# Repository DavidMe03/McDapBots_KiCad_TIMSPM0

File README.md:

# McDap Bots Pedagogical Robot

This project was created as a capstone project for the University of Virginia Department of Electrical and Computer Engineering. Our goal was to create a small robot which could be programmed by students, for use as a teaching aide in an embedded systems course. This repository contains the hardware files specific to the robot's main board.

**Authors**
- Colby Wise
- Pratik Pandit
- Austen Yun 
- David Merino
- Marc Rosenthal

**Advisors**: Todd DeLong and Adam Barnes 

**Features at a glance**
- 2 motors (PWM controlled), OLED screen (I2C), reflectance sensor (I2C), bump switches (GPIO), Bluetooth (UART), and infrared sensors (ADC)
- battery charging port and battery voltage display (press button to enable)
- support for TI and STM microcontrollers

## What is contained here

**Project Symbols/Footprints**

Symbols that are specific to this project such as the robot chassis. 

**Schematic File**

KiCad schematic file that shows the electrical connections of each component of the robot. 

**Layout File**

KiCad layout file that shows how the components are placed and routed on the PCB. 

**Bill of Materials Files**

BOM.xlsx contains a list of all the parts needed for the PCB.

Digikey_Parts_List.xlsx can be uploaded to Digikey to select the parts needed for one copy of this board.

## How to use this repository
1. Copy the repository locally to your computer
2. Using KiCad 8.0 (or higher version) open the file `MotorBoardv3_2.kicad_pro`
3. Generate necessary gerber files and order components
4. Follow the provided construction guide to build the robot

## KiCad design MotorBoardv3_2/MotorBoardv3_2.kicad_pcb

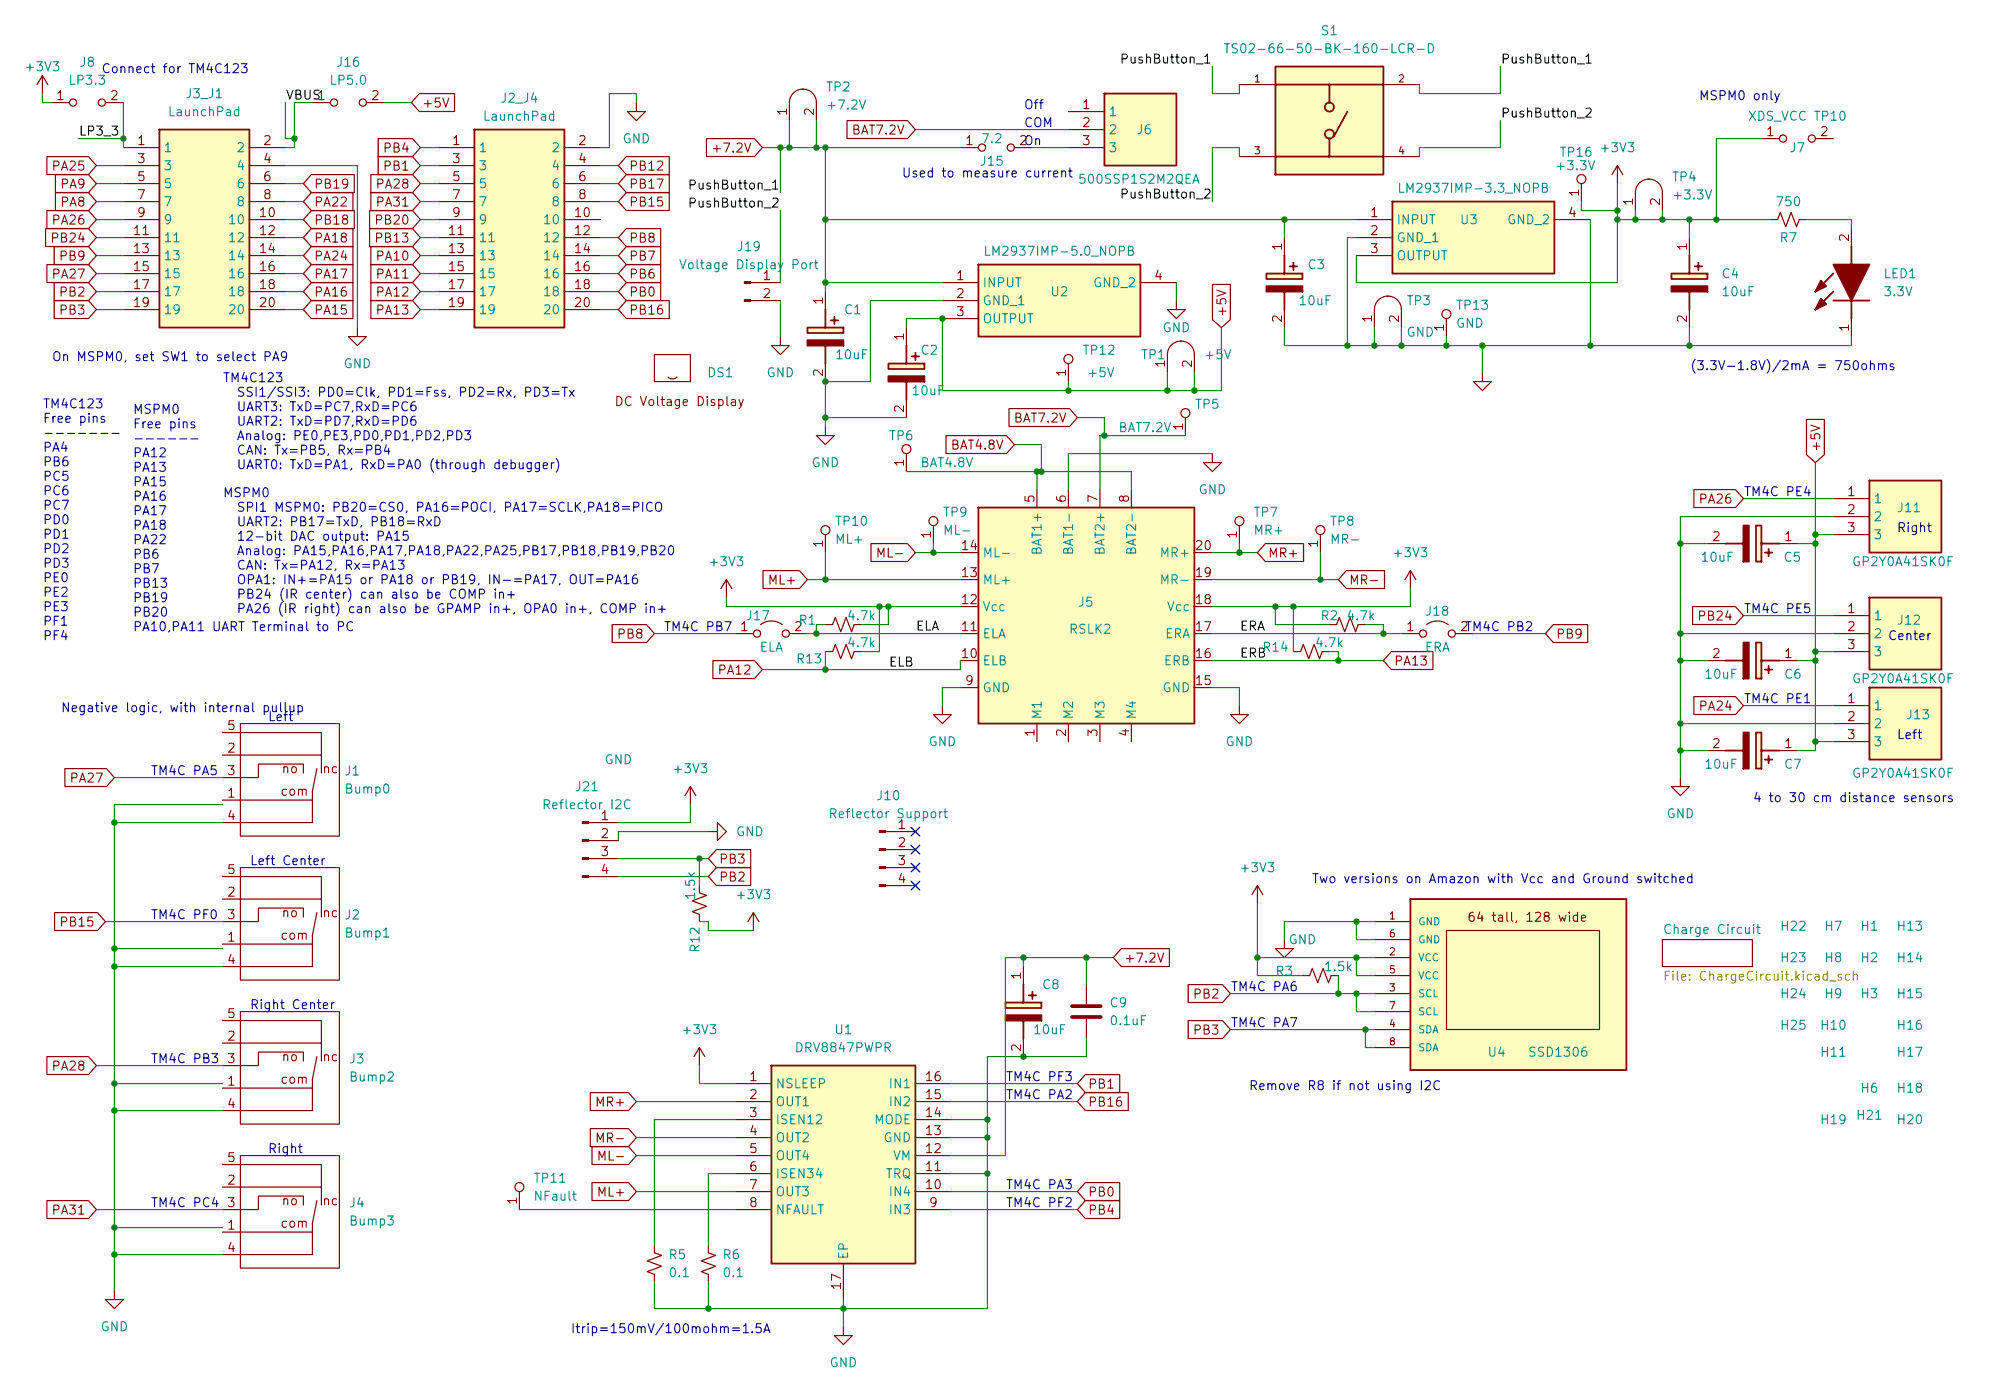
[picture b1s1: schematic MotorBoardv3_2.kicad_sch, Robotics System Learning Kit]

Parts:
C1, C2, C3, C4, C5, C6, C7, C8: 10uF; CAPPM3528X210N; Mouser Part Number 581-TAJB106K020R
C9: 0.1uF; C_0603_1608Metric; LCSC C5186689
DS1: PRT-14313
H1, H2, H3, H6, H7, H8, H9, H10, H11, H13, H14, H15, H16, H17, H18, H19, H20, H21, H22, H23, H24, H25: MountingHole_4_40
J1: Bump0; D2F-01L30-D3_5pin
J2: Bump1; D2F-01L30-D3_5pin
J2_J4, J3_J1: LaunchPad; Mouser Part Number 855-M20-8761042P
J3: Bump2; D2F-01L30-D3_5pin
J4: Bump3; D2F-01L30-D3_5pin
J5: RSLK2; RSLK_Chassis
J6: 500SSP1S2M2QEA; Mouser Part Number 612-500SSP1S2M2QEA
J7: XDS_VCC TP10; PinHeader_1x02_P2.54mm_Vertical; LCSC C5172712
J8: LP3.3; PinHeader_1x02_P2.54mm_Vertical; LCSC C5172712
J10: Reflector Support; PinHeader_1x04_P2.54mm_Vertical
J11, J12, J13: GP2Y0A41SK0F; SHDR3W50P0X200_1X3_650X240X440P; Mouser Part Number 855-M22-7130342
J15: 7.2; PinHeader_1x02_P2.54mm_Vertical; LCSC C5172712
J16: LP5.0; PinHeader_1x02_P2.54mm_Vertical; LCSC C5172712
J17: ELA; PinHeader_1x02_P2.54mm_Vertical
J18: ERA; PinHeader_1x02_P2.54mm_Vertical
J19: Voltage Display Port; SolderWire-0.15sqmm_1x02_P4mm_D0.5mm_OD1.5mm_Relief
J21: Reflector I2C; PinHeader_1x04_P2.54mm_Vertical
LED1: 3.3V; APT1608CGCK; Mouser Part Number 604-APTD1608LSECKJ3F
R1, R2, R13, R14: 4.7k; R_0603_1608Metric; LCSC C23162
R3, R12: 1.5k; R_0603_1608Metric; LCSC C216914
R5, R6: 0.1; R_1206_3216Metric; LCSC C2889036
R7: 750; R_0603_1608Metric; LCSC C365210
S1: TS02-66-50-BK-160-LCR-D; SW_TS02-66-50-BK-160-LCR-D; PARTREV 1.0
TP1: +5V; Testpoint_1x02_P2.54mm
TP2: +7.2V; Testpoint_1x02_P2.54mm
TP3: GND; Testpoint_1x02_P2.54mm
TP4: +3.3V; Testpoint_1x02_P2.54mm
TP5: BAT7.2V; Testpoint_1x1
TP6: BAT4.8V; Testpoint_1x1
TP7: MR+; Testpoint_1x1
TP8: MR-; Testpoint_1x1
TP9: ML-; Testpoint_1x1
TP10: ML+; Testpoint_1x1
TP11: NFault; Testpoint_1x1
TP12: +5V; Testpoint_1x1
TP13: GND; Testpoint_1x1
TP16: +3.3V; Testpoint_1x1
U1: DRV8847PWPR; SOP65P640X120-17N; Mouser Part Number 595-DRV8847PWPR
U2: LM2937IMP-5.0_NOPB; SOT230P700X180-4N; Mouser Part Number 926-LM2937IMP5.0NOPB
U3: LM2937IMP-3.3_NOPB; SOT230P700X180-4N; Mouser Part Number 926-LM2937IMP3.3NOPB
U4: SSD1306

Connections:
+3V3: C4.1 (+), J5.12 (Vcc), J5.18 (Vcc), J7.1 (A), J8.1 (A), J21.1, R1.2, R2.1, R3.1, R7.2, R12.1, R13.2, R14.1, TP4.1 (A), TP4.2 (B), TP16.1 (A), U1.1 (NSLEEP), U3.3 (OUTPUT), U4.2 (VCC), U4.5 (VCC)
+5V: C2.1 (+), C5.1 (+), C6.1 (+), C7.1 (+), J11.3, J12.3, J13.3, J16.2 (B), TP1.1 (A), TP1.2 (B), TP12.1 (A), U2.3 (OUTPUT)
+7.2V: C1.1 (+), C3.1 (+), C8.1 (+), C9.1, J15.1 (A), S1.1, S1.2, TP2.1 (A), TP2.2 (B), U1.12 (VM), U2.1 (INPUT), U3.1 (INPUT)
/ELA: J5.11 (ELA), J17.2 (B), R1.1
/ERA: J5.17 (ERA), J18.1 (A), R2.2
/LP3_3: J3_J1.1, J8.2 (B)
/PushButton_2: J19.1, S1.3, S1.4
/VBUS: J3_J1.2, J16.1 (A)
BAT4.8V: J5.5 (BAT1+), J5.8 (BAT2-), TP6.1 (A)
BAT7.2V: J5.7 (BAT2+), J6.2, TP5.1 (A); also elsewhere on the board
GND: C1.2 (-), C2.2 (-), C3.2 (-), C4.2 (-), C5.2 (-), C6.2 (-), C7.2 (-), C8.2 (-), C9.2, J1.4 (com), J2.4 (com), J2_J4.2, J3.4 (com), J3_J1.4, J4.4 (com), J5.6 (BAT1-), J5.9 (GND), J5.15 (GND), J11.2, J12.2, J13.2, J19.2, J21.2, LED1.1 (K), R5.2, R6.2, TP3.1 (A), TP3.2 (B), TP13.1 (A), U1.11 (TRQ), U1.13 (GND), U1.14 (MODE), U1.17 (EP), U2.2 (GND_1), U2.4 (GND_2), U3.2 (GND_1), U3.4 (GND_2), U4.1 (GND), U4.6 (GND); also elsewhere on the board
ML+: J5.13 (ML+), TP10.1 (A), U1.7 (OUT3)
ML-: J5.14 (ML-), TP9.1 (A), U1.5 (OUT4)
MR+: J5.20 (MR+), TP7.1 (A), U1.2 (OUT1)
MR-: J5.19 (MR-), TP8.1 (A), U1.4 (OUT2)
unnamed: J6.3, J15.2 (B)
unnamed: LED1.2 (A), R7.1
unnamed: TP11.1 (A), U1.8 (NFAULT)
unnamed: R5.1, U1.3 (ISEN12)
unnamed: R6.1, U1.6 (ISEN34)
PA8: J3_J1.7
PA9: J3_J1.5
PA10: J2_J4.13
PA11: J2_J4.15
PA12: J2_J4.17, J5.10 (ELB), R13.1
PA13: J2_J4.19, J5.16 (ERB), R14.2
PA15: J3_J1.20
PA16: J3_J1.18
PA17: J3_J1.16
PA18: J3_J1.12
PA22: J3_J1.8
PA24: J3_J1.14, J13.1
PA25: J3_J1.3
PA26: J3_J1.9, J11.1
PA27: J1.3 (no), J3_J1.15
PA28: J2_J4.5, J3.3 (no)
PA31: J2_J4.7, J4.3 (no)
PB0: J2_J4.18, U1.10 (IN4)
PB1: J2_J4.3, U1.16 (IN1)
PB2: J3_J1.17, J21.4, R3.2, U4.3 (SCL), U4.7 (SCL)
PB3: J3_J1.19, J21.3, R12.2, U4.4 (SDA), U4.8 (SDA)
PB4: J2_J4.1, U1.9 (IN3)
PB6: J2_J4.16
PB7: J2_J4.14
PB8: J2_J4.12, J17.1 (A)
PB9: J3_J1.13, J18.2 (B)
PB12: J2_J4.4
PB13: J2_J4.11
PB15: J2.3 (no), J2_J4.8
PB16: J2_J4.20, U1.15 (IN2)
PB17: J2_J4.6
PB18: J3_J1.10
PB19: J3_J1.6
PB20: J2_J4.9
PB24: J3_J1.11, J12.1

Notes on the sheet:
TM4C PB7
TM4C PE5
Negative logic, with internal pullup
TM4C PF2
TM4C PC4
Used to measure current
Right
TM4C PA3
MSPM0 Free pins ------ PA12 PA13 PA15 PA16 PA17 PA18 PA22 PB6 PB7 PB13 PB19 PB20 PA10,PA11 UART Terminal to PC
TM4C PB2
TM4C123 Free pins ------- PA4 PB6 PC5 PC6 PC7 PD0 PD1 PD2 PD3 PE0 PE2 PE3 PF1 PF4
Left Center
Connect for TM4C123
Left
TM4C PF3
TM4C PA6
MSPM0 SPI1 MSPM0: PB20=CS0, PA16=POCI, PA17=SCLK,PA18=PICO UART2: PB17=TxD, PB18=RxD 12-bit DAC output: PA15 Analog: PA15,PA16,PA17,PA18,PA22,PA25,PB17,PB18,PB19,PB20 CAN: Tx=PA12, Rx=PA13 OPA1: IN+=PA15 or PA18 or PB19, IN-=PA17, OUT=PA16 PB24 (IR center) can also be COMP in+ PA26 (IR right) can a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
TM4C PF0
Two versions on Amazon with Vcc and Ground switched
Itrip=150mV/100mohm=1.5A
TM4C PA5
Off
4 to 30 cm distance sensors
On MSPM0, set SW1 to select PA9
Remove R8 if not using I2C
Right Center
Center
TM4C PE4
(3.3V-1.8V)/2mA = 750ohms
TM4C PB3
TM4C PA7
MSPM0 only
COM
TM4C PE1
TM4C PA2
TM4C123 SSI1/SSI3: PD0=Clk, PD1=Fss, PD2=Rx, PD3=Tx UART3: TxD=PC7,RxD=PC6 UART2: TxD=PD7,RxD=PD6 Analog: PE0,PE3,PD0,PD1,PD2,PD3 CAN: Tx=PB5, Rx=PB4 UART0: TxD=PA1, RxD=PA0 (through debugger)

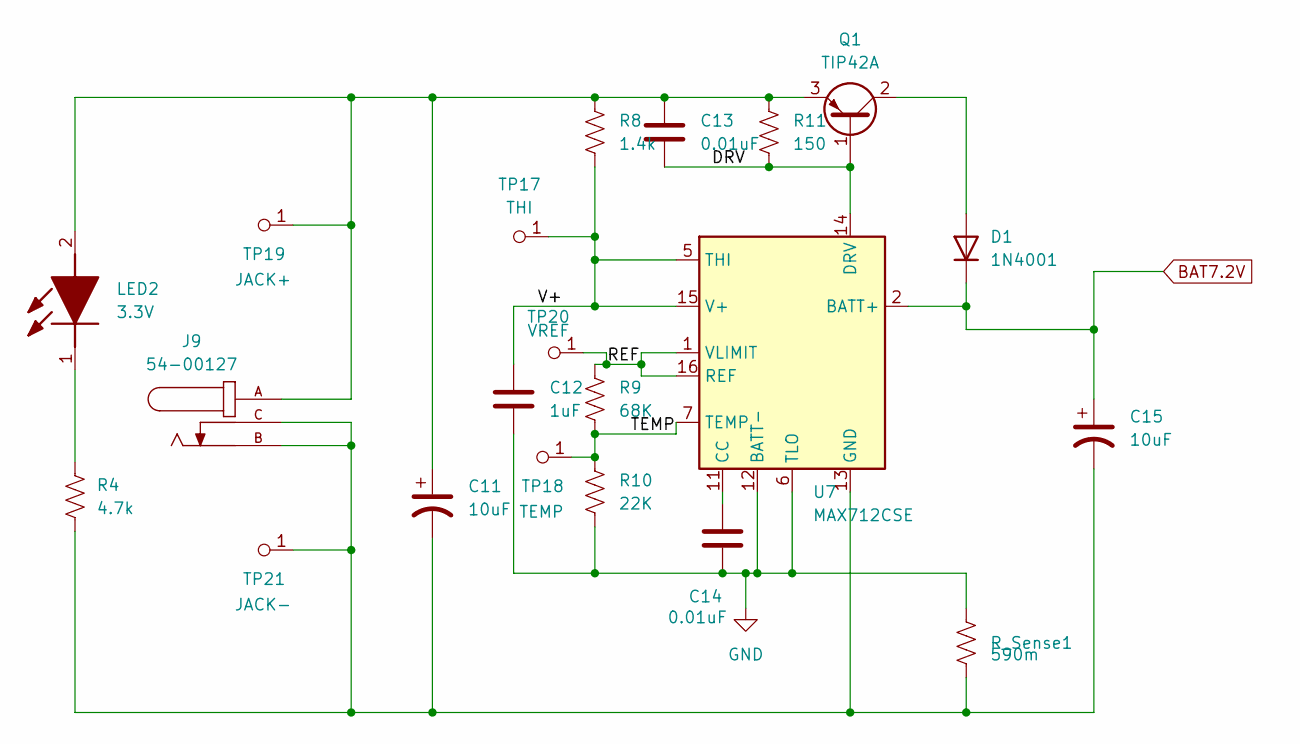
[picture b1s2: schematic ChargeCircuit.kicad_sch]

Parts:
C11, C15: 10uF; C_0603_1608Metric
C12: 1uF; C_0603_1608Metric
C13, C14: 0.01uF; C_0603_1608Metric
D1: 1N4001; D_DO-41_SOD81_P10.16mm_Horizontal
J9: 54-00127; TENSILITY_54-00127; PARTREV A
LED2: 3.3V; APT1608CGCK; Mouser Part Number 604-APTD1608LSECKJ3F
Q1: TIP42A; TO-220-3_Vertical
R4: 4.7k; R_0603_1608Metric
R8: 1.4k; R_0603_1608Metric
R9: 68K; R_0603_1608Metric
R10: 22K; R_0603_1608Metric
R11: 150; R_0603_1608Metric
R_Sense1: 590m; R_0603_1608Metric
TP17: THI; Testpoint_1x1
TP18: TEMP; Testpoint_1x1
TP19: JACK+; Testpoint_1x1
TP20: VREF; Testpoint_1x1
TP21: JACK-; Testpoint_1x1
U7: MAX712CSE; SOIC-16_3.9x9.9mm_P1.27mm

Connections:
/Charge Circuit/DRV: C13.2, Q1.1 (B), R11.2, U7.14 (DRV)
/Charge Circuit/REF: R9.1, TP20.1 (A), U7.1 (VLIMIT), U7.16 (REF)
/Charge Circuit/TEMP: R9.2, R10.1, TP18.1 (A), U7.7 (TEMP)
/Charge Circuit/V+: C12.1, R8.2, TP17.1 (A), U7.5 (THI), U7.15 (V+)
BAT7.2V: C15.1, D1.1 (K), U7.2 (BATT+); also elsewhere on the board
GND: C12.2, C14.2, R10.2, R_Sense1.1, U7.6 (TLO), U7.12 (BATT-); also elsewhere on the board
unnamed: D1.2 (A), Q1.2 (C)
unnamed 22: C11.1, C13.1, J9.A, LED2.2 (A), Q1.3 (E), R8.1, R11.1, TP19.1 (A); also elsewhere on the board
unnamed 23: LED2.1 (K), R4.1; also elsewhere on the board
unnamed: C11.2, C15.2, J9.B, J9.C, R4.2, R_Sense1.2, TP21.1 (A), U7.13 (GND)
unnamed: C14.1, U7.11 (CC)

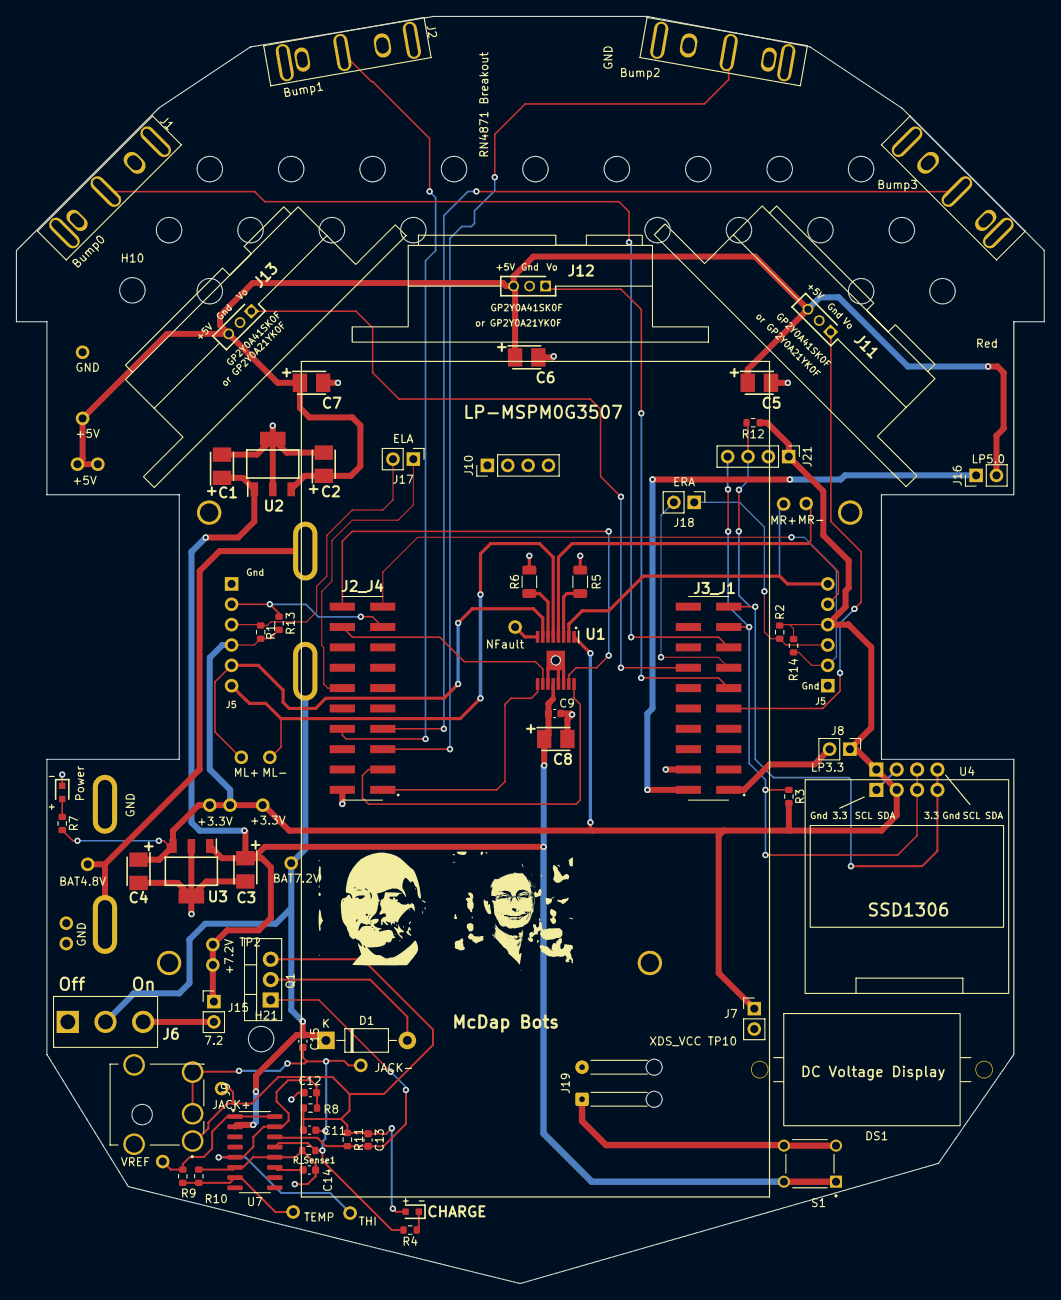
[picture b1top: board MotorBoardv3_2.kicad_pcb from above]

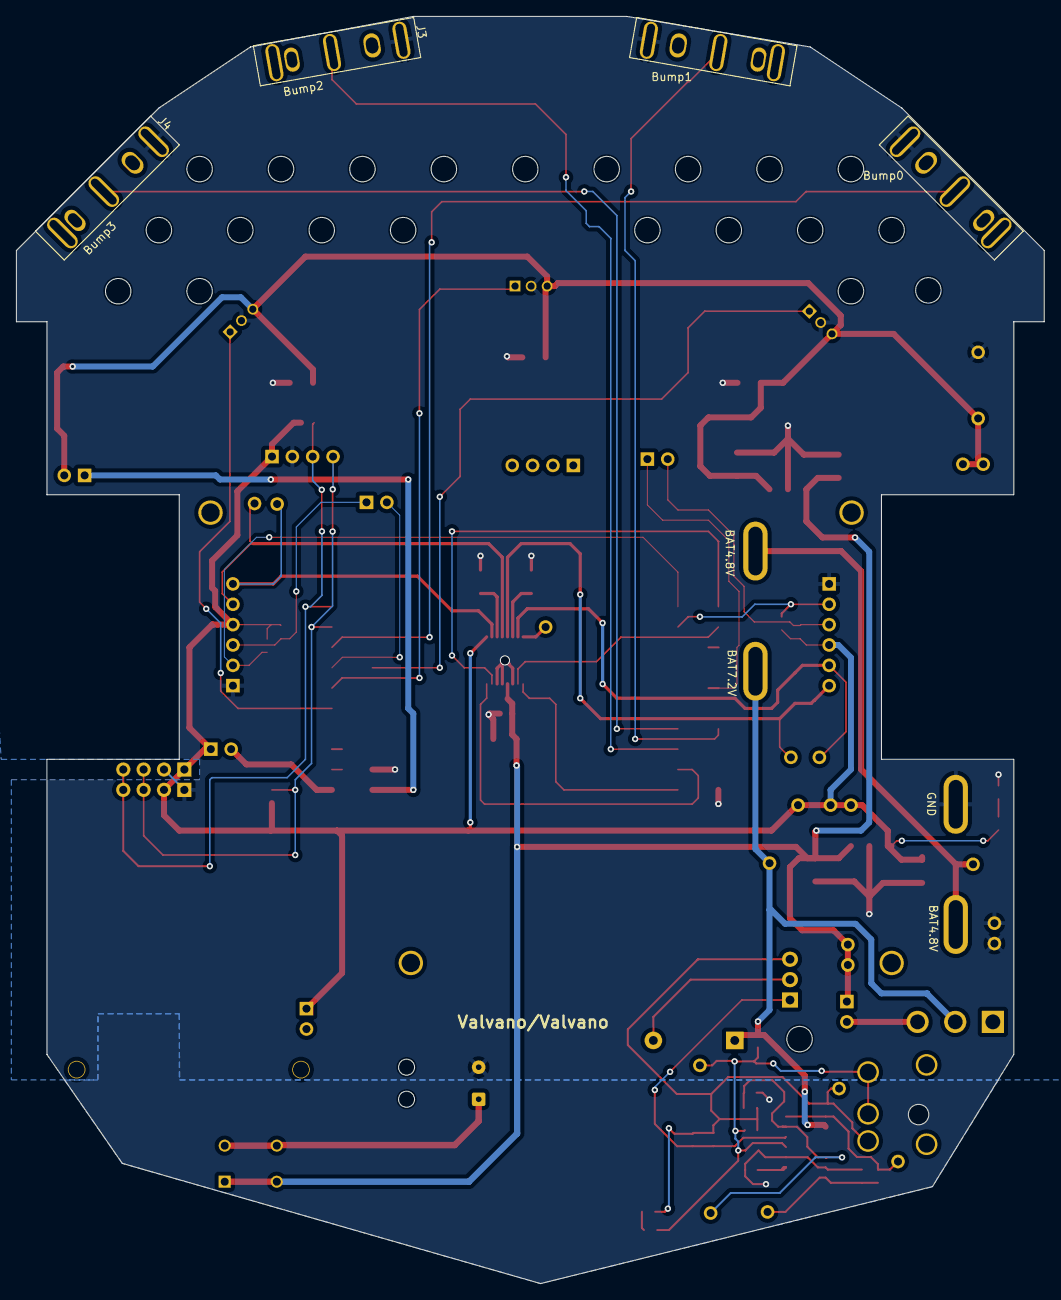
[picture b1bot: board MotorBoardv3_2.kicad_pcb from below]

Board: 2 copper layers, 128.3 x 158.1 mm, 102 parts (2 on the bottom side), 46 nets.

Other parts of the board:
CHARGE: 3.3V; APT1608CGCK

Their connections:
unnamed 22: CHARGE.2 (A); also elsewhere on the board
unnamed 23: CHARGE.1 (K); also elsewhere on the board

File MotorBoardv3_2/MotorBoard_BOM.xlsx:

Main PCB Parts
Id | Designator | Footprint | Quantity | Designation | Supplier | Link | Notes
1 | LED1 | APT1608CGCK | 1 | 3.3V | Digikey | APTD1608LSECK/J3-PF Kingbright | Optoelectronics | DigiKey | Red LED to indicate robot on/off
2 | CHARGE | APT1608CGCK | 1 | 3.3V | Digikey | APTD1608LZGCK Kingbright | Optoelectronics | DigiKey | Green LED to indicate battery charging
3 | R1,R2,R4,R13,R14 | R_0603_1608Metric | 5 | 4.7k | Digikey | RC0603FR-104K7L YAGEO | Resistors | DigiKey | Resistors
4 | R3,R12 | R_0603_1608Metric | 2 | 1.5k | Digikey | RC0603FR-071K5L YAGEO | Resistors | DigiKey | Resistors
5 | R5,R6 | R_1206_3216Metric | 2 | 0.1 | Digikey | RCWL1206R100JMEA Vishay Dale | Resistors | DigiKey | Resistors
6 | R7 | R_0603_1608Metric | 1 | 750 | Digikey | RC0603JR-07750RL YAGEO | Resistors | DigiKey | Resistor
7 | R8 | R_0603_1608Metric | 1 | 1.4k | Digikey | RC0603FR-071K4L YAGEO | Resistors | DigiKey | Resistor
8 | R9 | R_0603_1608Metric | 1 | 68K | Digikey | RT0603FRE0768KL YAGEO | Resistors | DigiKey | Resistor
9 | R10 | R_0603_1608Metric | 1 | 22K | Digikey | RC0603JR-0722KL YAGEO | Resistors | DigiKey | Resistor
10 | R11 | R_0603_1608Metric | 1 | 150 | Digikey | RMCF0603FT150R Stackpole Electronics Inc | Resistors | DigiKey | Resistor
11 | R_Sense1 | R_0603_1608Metric | 1 | 590m | Digikey | RLT0816-3-R590-FNH Delta Electronics/Cyntec | Resistors | DigiKey | Resistor
12 | C1,C2,C3,C4,C5,C6,C7,C8 | CAPPM3528X210N | 8 | 10uF | Digikey | TAJB106K020RNJ KYOCERA AVX | Capacitors | DigiKey | Capacitors (Polar)
13 | C9 | C_0603_1608Metric | 1 | 0.1uF | Digikey | CC0603KRX7R7BB104 YAGEO | Capacitors | DigiKey | Capacitor
14 | C11,C15 | C_0603_1608Metric | 2 | 10uF | Digikey | TCM0J106M8R KYOCERA AVX | Capacitors | DigiKey | Capacitors (Polar)
15 | C12 | C_0603_1608Metric | 1 | 1uF | Digikey | CL10B105KP8NNNC Samsung Electro-Mechanics | Capacitors | DigiKey | Capacitor
16 | C13,C14 | C_0603_1608Metric | 2 | 0.01uF | Digikey | C0603C103K5RACTU KEMET | Capacitors | DigiKey | Capacitors
17 | D1 | D_DO-41_SOD81_P10.16mm_Horizontal | 1 | 1N4001 | Digikey | 1N4001-TP MCC (Micro Commercial Components) | Discrete Semiconductor Products |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 | Rectifier Diode
18 | Q1 | TO-220-3_Vertical | 1 | TIP42A | Digikey | TIP42A STMicroelectronics | Discrete Semiconductor Products | DigiKey | PNP Transistor
19 | U1 | SOP65P640X120-17N | 1 | DRV8847PWPR | Digikey | DRV8847PWR Texas Instruments | Integrated Circuits (ICs) | DigiKey | Motor Driver IC
20 | U2 | SOT230P700X180-4N | 1 | LM2937IMP-5.0_NOPB | Digikey | LM2937IMP-5.0/NOPB Texas Instruments | Integrated Circuits (ICs) | DigiKey | 5V Linear Regulator IC
21 | U3 | SOT230P700X180-4N | 1 | LM2937IMP-3.3_NOPB | Digikey | LM2937IMP-3.3 Texas Instruments | Integrated Circuits (ICs) | DigiKey | 3.3V Linear Regulator IC
22 | U4 | SSD1306 | 1 | SSD1306 | Amazon | Amazon.com: Hosyond 5 Pcs 0.96 Inch OLED I2C IIC Display Module 12864 128x64 Pi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 | OLED Display Board, can be soldered directly onto PCB
23 | U7 | SOIC-16_3.9x9.9mm_P1.27mm | 1 | MAX712CSE | Digikey | MAX712CSE+T Analog Devices Inc./Maxim Integrated | Integrated Circuits (ICs) | 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 | Charge Controller IC
24 | DS1 | PRT-14313 | 1 | ~ | Digikey | 14313 SparkFun Electronics | Industrial Automation and Controls | DigiKey | Voltmeter LED Display
25 | S1 | SW_TS02-66-50-BK-160-LCR-D | 1 | TS02-66-50-BK-160-LCR-D | Digikey | TS02-66-50-BK-160-LCR-D Same Sky (Formerly CUI Devices) | Switches | DigiKey | SPST Tactile Switch for voltmeter
26 | J6 | 500SSP1S2M2QEA | 1 | 500SSP1S2M2QEA | Digikey | 500SSP1S2M2QEA E-Switch | Switches | DigiKey | Robot power on/off slide switch
27 | J9 | TENSILITY_54-00127 | 1 | 54-00127 | Digikey | 54-00127 Tensility International Corp | Connectors, Interconnects | DigiKey | DC barrel jack port
28 | J2_J4,J3_J1 | LaunchPad | 2 | LaunchPad | Digikey | M20-8761042P Harwin Inc. | Connectors, Interconnects | DigiKey | 20 position headers for connecting to the TI Launchpad
29 | J11,J12,J13 | SHDR3W50P0X200_1X3_650X240X440P | 3 | GP2Y0A41SK0F | Digikey | M22-7130342 Harwin Inc. | Connectors, Interconnects | DigiKey | Female header pins for the IR Sensors
30 | J1,J2,J3,J4 | D2F-01L30-D3_5pin | 4 | Bump1,Bump2,Bump3,Bump4 | Digikey | SS-5GL2 Omron Electronics Inc-EMC Div | Switches | DigiKey | Bump switches
31 | J5 | RSLK_Chassis | 2 | RSLK2 | Digikey | CES-106-01-G-S Samtec Inc. | Connectors, Interconnects | DigiKey | Female header pins for the motors
32 | J10,J21 | PinHeader_1x04_P2.54mm_Vertical | 2 | Reflector Support, Reflector I2C | Digikey | PPTC041LFBN-RC Sullins Connector Solutions | Connectors, Interconnects | DigiKey | Female header pins for the reflectance sensor array
33 | J7,J8,J15,J16,J17,J18 | PinHeader_1x02_P2.54mm_Vertical | 6 | XDS_VCC TP10, LP3.3,7.2,LP5.0,ELA,ERA | Digikey | TSW-120-07-L-S Samtec Inc. | Connectors, Interconnects | DigiKey | Male header pins for jumpers
34 | TP1,TP2,TP3,TP4 | Testpoint_1x02_P2.54mm | 4 | +5V,+7.2V,GND,+3.3V | Digikey | TSW-120-07-L-S Samtec Inc. | Connectors, Interconnects | DigiKey | Male header pins for test points
Additional Parts
Id | Designator | Footprint | Quantity | Designation | Supplier | Link | Notes
1 |  |  | 3 | IR Sensors | Digikey | GP2Y0A21YK0F SHARP/Socle Technology | Sensors, Transducers | DigiKey | 10-80cm IR Sensors
2 |  |  | 1 | Romi Chassis Kit | Pololu | Pololu - Romi Chassis Kit - Black | Robot chassis, wheels, motors, battery contacts
3 |  |  | 1 | Romi Encoder Pair Kit | Pololu | Pololu - Romi Encoder Pair Kit, 12 CPR, 3.5-18V | Pair of motor encoders
4 |  |  | 1 | TI MSPM0 Launchpad | Texas Instruments | LP-MSPM0G3507 Evaluation board | TI.com | MSPM0 Launchpad, development board for the TI microcontroller
5 |  |  | 6 | Shunts | Digikey | 382811-8 TE Connectivity AMP Connectors | Connectors, Interconnects | DigiKey | Shunts for the jumpers
6 |  |  | 1 | Launchpad Power Connector | Digikey | SSQ-102-01-G-S Samtec Inc. | Connectors, Interconnects | DigiKey | 2-pin female header soldered onto the MSPM0 Launchpad

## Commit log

2025-09-19 Added voltage display
    Modified schematic and layout to include voltage display. Expanded board outline in layout to have more space at the back of the robot.
2025-09-23 Added charge controller schematic
2025-09-23 added bluetooth module to schematic
2025-09-24 Completed Schematic w/ charge circuit, voltmeter, bluetooth, Reflective Sensor Port
2025-09-28 corrected david's silly label
2025-09-28 deleted esp8266 and tf-luna circuits from schematic
2025-09-28 Fixed David's creative file path choices
2025-09-28 Deleted traces and text from ESP and Luna
2025-09-28 Fixed footprint not in library error
2025-09-28 Filled in ground plane where needed
2025-09-28 Created footprint for RN4871 through-hole
2025-09-29 Initial Charge Controller layout
2025-09-29 Label adjustements
2025-09-30 routed RN4871 eval board pins
    Also changed the positions of some silkscreen labels
2025-09-30 Added voltage display
2025-09-30 Added I2C port for reflective sensors
2025-09-30 changed I2C port placement on schematic
2025-10-01 Removed uncessary ground trace
2025-10-01 Fixed DRC errors
2025-10-01 Fixed some silkscreen labels
2025-10-01 Increased trace widths
    Increased trace widths of 3.3V and GND signals going to Bluetooth module
2025-10-01 Added test points to Charge Circuit
2025-10-02 Changed Barrel Jack Footprint to incorporate through-hole connections
2025-10-02 Updated Labeling so Silkscreen is not offboard; Added some necessary changes
2025-10-03 Generated Gerber Files
2025-10-03 Removed bottom silkscreen from gerbers
    Regenerated gerbers to not include bottom silkscreen layer
2025-11-06 i closed the project this time
2025-11-06 Removed old bluetooth module from schematic and layout
2025-11-06 added voltmeter button to schematic
2025-11-06 added a possible footprint for button
2025-11-06 added button for DC Display
2025-11-06 Moved the transistor to not be under the MSPM0G3507
2025-11-06 test
2025-11-07 Added reflector sensor support pins to schematic and layout
2025-11-07 Changed pin usages for rev 2
2025-11-07 added pullup resistors to encoders
2025-11-08 Fixed right motor header location
    Still need to move some traces around
2025-11-09 Updated traces
2025-11-10 added charging indicator led
2025-11-11 added charge LED to layout
2025-11-11 Generated Gerbers
    Also modified silkscreen to indicate polarity of diode
2025-12-12 Created README.md
2025-12-18 Fix typo in README instructions
2025-12-18 Added BOM files
